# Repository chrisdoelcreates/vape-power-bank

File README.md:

# Disposable Vape Powerbank Project

This repository contains everything you need to build a functional 100W power bank using lithium-ion cells salvaged from disposable vapes.

## 📺 Watch the Video

See the entire build process in action on my YouTube channel:

[Watch on YouTube](https://youtu.be/kMiJdfgIfqI)

---

This powerbank is an upgrade from my [initial design](https://www.youtube.com/watch?v=ehp23hrrEHY) and is now smaller, lighter, safer, and easier to assemble.
It’s a fantastic way to repurpose vape batteries and contribute to reducing e-waste while learning valuable electronics and 3D printing skills.

---

## ⚠️ Disclaimer

This project involves handling lithium-ion batteries, which can be dangerous if mishandled. By using these designs or instructions, you acknowledge and agree to the following:

- You assume all risks associated with the assembly and use of this project.
- This project is provided "as-is," with no guarantees of safety or performance.
- Always take appropriate safety precautions and seek professional guidance if unsure.

Please read the full [Disclaimer](DISCLAIMER.md) before proceeding.

---

## Affiliate Links & Sponsorship Disclosure

This repository contains affiliate links to suppliers and services. If you use these links to purchase parts (from Aliexpress) or sign up for services (such as JLCPCB), I may earn a small commission at no extra cost to you. These links help support the development of this project and my YouTube channel.

Thank you for supporting my work!

---

## 🚀 Project Overview

In this project, you will:
- Extract lithium-ion cells from disposable vapes.
- Test and prepare the cells for use.
- Assemble a 3D-printed cell holder and enclosure.
- Install custom PCBs to balance charge the cells and wire them up to form a 5S7P (5 cells in series, 7 cells in parallel) battery pack.
- Wire up a fast-charge USB powerbank board.

### Key Features:
- Doesn't require directly soldering the cells together.
- Multifunction PCBs (balance charging and power delivery) to reduce parts cost.
- Open-source PCBs & 3D prints for easy customization and collaboration.
- Supports 100W USB C PD charging.
---

## 📂 Repository Contents

This repository is organized as follows:
```
Disposable-Vape-Powerbank/
├── README.md           # Introduction and instructions
├── DISCLAIMER.md       # Full project disclaimer
├── LICENSE             # Project licensing details
├── PCB-Files/          # PCB related files
│   ├── Production-Files/   # PCB files for ordering
│   ├── Schematic.pdf       # PCB schematic
│   └── KiCad_Project/      # KiCAD project files
├── 3D-Models/          # Fusion360 files and links to printables
└── Images/             # Photos and renders of the project
```
## 🛠️ Quick Start Guide

Follow these steps to build your own disposable vape power bank:

1. *Download Files*
   - Click the green *Code* button and select *Download ZIP*. Then extract the repository files.
   - or clone the repository:
     git clone [https://github.com/username/Disposable-Vape-Powerbank.git](https://github.com/chrisdoelcreates/vape-power-bank)
     
2. *Order the PCBs*
    - Head over to [JLCPCB](https://jlcpcb.com/?from=cdd) (or any other PCB ordering site)
    - Sign up/Log in
    - Head to the order page
    - Upload the Gerber file from Disposable-Vape-Powerbank/PCB-Files/Production-Files/
    - Refer to 10:13 in the [project video](https://youtu.be/h3FRk3OD1Ug) for order settings
    - Ensure 'Assembly' is checked
    - Upload the CPL and BOM files
    - Rotate the connectors to match the orientation within the video
    - Place the order!
  *If you get an email asking if the polarities of the springs are correct - reply that they are*

3. *Order the USB board*
    - [USB board - Type 1 (Recommended - Used in the video)](https://s.click.aliexpress.com/e/_oBGOqhR)
       - *ENSURE THE 5S OPTION IS SELECTED*
    - [USB board - Type 2 (More USB C ports - requires different 3D prints to the video)](https://s.click.aliexpress.com/e/_oBXyxIH)
       - *ENSURE THE 5S OPTION IS SELECTED*

4. *Order the conductive tape*
    - [Conductive tape](https://s.click.aliexpress.com/e/_olaCL05)
       - *ENSURE the '10mm' & 'Conductive on both sides' options are selected*

5. *Order optional extras*
    - [Right angle JST connector](https://s.click.aliexpress.com/e/_oEeP6lf)
      - *ENSURE XH2.54MM, Length 10CM, 4P IS SELECTED*
      - Not essential but makes wiring the board slightly easier
    - [8 Channel Cell Tester](https://s.click.aliexpress.com/e/_oEuMn9T)
      - Also not essential
      - Allows you to match the battery capacities for each parallel row - improves powerbank battery life & lifespan
      - Good if you regularly do battery related projects

6. *Print the parts*
    - Easiest: Find the right size on [printables](https://www.printables.com/@montecha_2397581/collections/2035794)
      Or
    - Download the cell holder from the 3D models folder
    - Download the enclosure from the 3D models folder
      - Select the enclosure depending on your board type
    - Print out the parts!

7. *Build the Powerbank!*
     - Follow along with the Youtube video

---

## 🧾 Licensing

This project is licensed under the [MIT License](LICENSE). You are free to use, modify, and distribute the files, provided you include proper attribution and accept the project’s disclaimers.

---

## 🤝 Contributions

Contributions are welcome! If you have suggestions, improvements, or issues, feel free to:
- Open an issue in this repository.
- Submit a pull request with your changes.

---

## 🌟 Acknowledgments

A big thank you to:
- *JLCPCB* for sponsoring the youtube video/project.
- Everyone who has supported and engaged with my Youtube channel.

---

Enjoy building your power bank and contributing to e-waste reduction!

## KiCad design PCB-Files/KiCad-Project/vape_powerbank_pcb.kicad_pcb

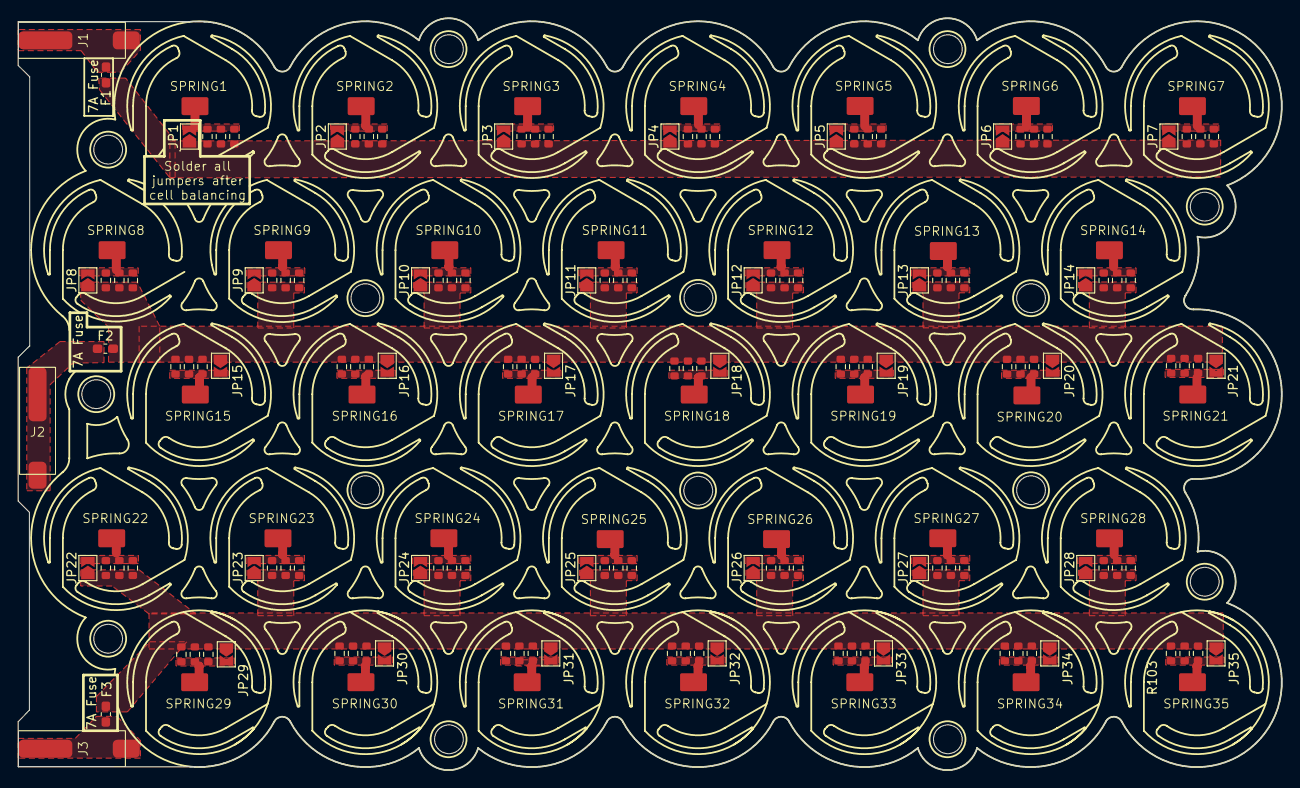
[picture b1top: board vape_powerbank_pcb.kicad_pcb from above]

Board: 2 copper layers, 140.6 x 83.6 mm, 181 parts (0 on the bottom side), 41 nets.

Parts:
F1, F2, F3: Fuse; Fuse_0603_1608Metric_Pad1.05x0.95mm_HandSolder
J1, J2, J3: Conn_01x01_Pin; SMD_spring_clamp_connector_1x1
JP1, JP2, JP3, JP4, JP5, JP6, JP7, JP8, JP9, JP10, JP11, JP12, JP13, JP14, JP15, JP16, JP17, JP18, JP19, JP20, JP21, JP22, JP23, JP24, JP25, JP26, JP27, JP28, JP29, JP30, JP31, JP32, JP33, JP34, JP35: SolderJumper_2_Open; SolderJumper-2_P1.3mm_Open_TrianglePad1.0x1.5mm
R1, R2, R3, R4, R5, R6, R7, R8, R9, R10, R11, R12, R13, R14, R15, R16, R17, R18, R19, R20, R21, R22, R23, R24, R25, R26, R27, R28, R29, R30, R31, R32, R33, R34, R35, R36, R37, R38, R39, R40, R41, R42, R43, R44, R45, R46, R47, R48, R49, R50, R51, R52, R53, R54, R55, R56, R57, R58, R59, R60, R61, R62, R63, R64, R65, R66, R67, R68, R69, R70, R71, R72, R73, R74, R75, R76, R77, R78, R79, R80, R81, R82, R83, R84, R85, R86, R87, R88, R89, R90, R91, R92, R93, R94, R95, R96, R97, R98, R99, R100, R101, R102, R103, R104, R105: R; R_0603_1608Metric
SPRING1, SPRING2, SPRING3, SPRING4, SPRING5, SPRING6, SPRING7, SPRING8, SPRING9, SPRING10, SPRING11, SPRING12, SPRING13, SPRING14, SPRING15, SPRING16, SPRING17, SPRING18, SPRING19, SPRING20, SPRING21, SPRING22, SPRING23, SPRING24, SPRING25, SPRING26, SPRING27, SPRING28, SPRING29, SPRING30, SPRING31, SPRING32, SPRING33, SPRING34, SPRING35: spring_tab

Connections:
unnamed: F1.1, J1.1
unnamed: F2.1, J2.1
unnamed: F3.1, J3.1
unnamed: F1.2, JP1.1 (A), JP2.1 (A), JP3.1 (A), JP4.1 (A), JP5.1 (A), JP6.1 (A), JP7.1 (A), R1.2, R2.2, R3.2, R4.2, R5.2, R6.2, R7.2, R8.2, R9.2, R10.2, R11.2, R12.2, R13.2, R14.2, R15.2, R16.2, R17.2, R18.2, R19.2, R20.2, R21.2
unnamed: JP1.2 (B), R1.1, R2.1, R3.1, SPRING1.1
unnamed: JP2.2 (B), R4.1, R5.1, R6.1, SPRING2.1
unnamed: JP3.2 (B), R7.1, R8.1, R9.1, SPRING3.1
unnamed: JP4.2 (B), R10.1, R11.1, R12.1, SPRING4.1
unnamed: JP5.2 (B), R13.1, R14.1, R15.1, SPRING5.1
unnamed: JP6.2 (B), R16.1, R17.1, R18.1, SPRING6.1
unnamed: JP7.2 (B), R19.1, R20.1, R21.1, SPRING7.1
unnamed: JP8.2 (B), R22.1, R23.1, R24.1, SPRING8.1
unnamed: JP9.2 (B), R25.1, R26.1, R27.1, SPRING9.1
unnamed: F2.2, JP8.1 (A), JP9.1 (A), JP10.1 (A), JP11.1 (A), JP12.1 (A), JP13.1 (A), JP14.1 (A), JP15.1 (A), JP16.1 (A), JP17.1 (A), JP18.1 (A), JP19.1 (A), JP20.1 (A), JP21.1 (A), R22.2, R23.2, R24.2, R25.2, R26.2, R27.2, R28.2, R29.2, R30.2, R31.2, R32.2, R33.2, R34.2, R35.2, R36.2, R37.2, R38.2, R39.2, R40.2, R41.2, R42.2, R43.1, R44.1, R45.1, R46.1, R47.1, R48.1, R49.1, R50.1, R51.1, R52.1, R53.1, R54.1, R55.1, R56.1, R57.1, R58.1, R59.1, R60.1, R61.1, R62.1, R63.1
unnamed: JP10.2 (B), R28.1, R29.1, R30.1, SPRING10.1
unnamed: JP11.2 (B), R31.1, R32.1, R33.1, SPRING11.1
unnamed: JP12.2 (B), R34.1, R35.1, R36.1, SPRING12.1
unnamed: JP13.2 (B), R37.1, R38.1, R39.1, SPRING13.1
unnamed: JP14.2 (B), R40.1, R41.1, R42.1, SPRING14.1
unnamed: JP15.2 (B), R43.2, R44.2, R45.2, SPRING15.1
unnamed: JP16.2 (B), R46.2, R47.2, R48.2, SPRING16.1
unnamed: JP17.2 (B), R49.2, R50.2, R51.2, SPRING17.1
unnamed: JP18.2 (B), R52.2, R53.2, R54.2, SPRING18.1
unnamed: JP19.2 (B), R55.2, R56.2, R57.2, SPRING19.1
unnamed: JP20.2 (B), R58.2, R59.2, R60.2, SPRING20.1
unnamed: JP21.2 (B), R61.2, R62.2, R63.2, SPRING21.1
unnamed: F3.2, JP22.1 (A), JP23.1 (A), JP24.1 (A), JP25.1 (A), JP26.1 (A), JP27.1 (A), JP28.1 (A), JP29.1 (A), JP30.1 (A), JP31.1 (A), JP32.1 (A), JP33.1 (A), JP34.1 (A), JP35.1 (A), R64.2, R65.2, R66.2, R67.2, R68.2, R69.2, R70.2, R71.2, R72.2, R73.2, R74.2, R75.2, R76.2, R77.2, R78.2, R79.2, R80.2, R81.2, R82.2, R83.2, R84.2, R85.1, R86.1, R87.1, R88.1, R89.1, R90.1, R91.1, R92.1, R93.1, R94.1, R95.1, R96.1, R97.1, R98.1, R99.1, R100.1, R101.1, R102.1, R103.1, R104.1, R105.1
unnamed: JP22.2 (B), R64.1, R65.1, R66.1, SPRING22.1
unnamed: JP23.2 (B), R67.1, R68.1, R69.1, SPRING23.1
unnamed: JP24.2 (B), R70.1, R71.1, R72.1, SPRING24.1
unnamed: JP25.2 (B), R73.1, R74.1, R75.1, SPRING25.1
unnamed: JP26.2 (B), R76.1, R77.1, R78.1, SPRING26.1
unnamed: JP27.2 (B), R79.1, R80.1, R81.1, SPRING27.1
unnamed: JP28.2 (B), R82.1, R83.1, R84.1, SPRING28.1
unnamed: JP29.2 (B), R85.2, R86.2, R87.2, SPRING29.1
unnamed: JP30.2 (B), R88.2, R89.2, R90.2, SPRING30.1
unnamed: JP31.2 (B), R91.2, R92.2, R93.2, SPRING31.1
unnamed: JP32.2 (B), R94.2, R95.2, R96.2, SPRING32.1
unnamed: JP33.2 (B), R97.2, R98.2, R99.2, SPRING33.1
unnamed: JP34.2 (B), R100.2, R101.2, R102.2, SPRING34.1
unnamed: JP35.2 (B), R103.2, R104.2, R105.2, SPRING35.1

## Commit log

2025-01-09 Added kicad project & repo file structure
2025-01-10 Reduced fusable trace width to 0.3mm (~12A fusing current) and added images
2025-01-12 Added part links
2025-01-13 added 3D model files
2025-01-17 Updated video link
2025-01-17 Added conductive tape to BOM
2025-01-17 Added printables link
2025-01-18 Fix CPL so manual rotation of J1, J2, and J3 is no longer needed.
    Fix CPL so manual rotation of J1, J2, and J3 is no longer needed.
2025-01-18 Update positions to be more consistant to the official part
    positions updated to more closely match
    https://www.lcsc.com/product-detail/Spring-Clamp-System-Terminal-Block_HDGC-HDGC4001SMD-S-1P_C5197183.html
    https://www.lcsc.com/datasheet/lcsc_datasheet_2410121457_HDGC-HDGC4001SMD-S-1P_C5197183.pdf
